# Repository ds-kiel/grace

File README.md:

# IoT-Testbed

A very simple testbed for the IoT!

## GPIO Tracing

Please refer to `raspi/gpio-tracer` for our gpio tracing implementation.

## Installation

### for platform Zoul

It might be necessary to install `pyserial` and `libusb`:

```bash
sudo apt update
sudo apt install python3-pip -y
pip3 install pyserial

sudo apt install libusb-0.1-4
```

### preparation for platform nRF52840

#### COPY JLINK rules file to allow flashing nrf52 for non-root users

```bash
parallel-ssh --timeout 0 --hosts /usr/testbed/scripts/all-hosts --user user --inline "sudo cp /home/user/scripts/nrf52/JLink_Linux_arm/99-jlink.rules /etc/udev/rules.d"
```

#### Flash/Update JLINK Firmware

```bash
parallel-ssh --timeout 0 --hosts /usr/testbed/scripts/all-hosts --user user --inline "sudo -i && cd /home/user/scripts/nrf52 && ./install.sh null.nrf52.hex"
```

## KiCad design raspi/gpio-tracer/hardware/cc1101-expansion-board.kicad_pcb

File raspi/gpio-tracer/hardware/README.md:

# Description
This simple PCB can be used to wire together the development boards for easier
deployment. Alternatively, one can simply wire together everything using jumper wires. We produced
our PCBs at [JLCPCB](https://jlcpcb.com/), look below for our order configuration.
 The schematic files can be opened and exported to gerber files using
[KiCad](https://www.kicad.org/).  You can also look at the schematic for a reference as to how to
wire everything together.

# Hardware
## Receiver
We use a commonly available of-the-shelf cc1101 development board for our setup.  If you want to use
our circuit board for deployment, you need to get a board with the same pin-out configuration.  If
you don't want to use our board and use jumper wires instead, you can get one of the other commonly
available development boards. Just make sure that at least one GPIO (GDx) is exposed.

## Logic Analyzer
Use one of the commonly available ez-usb fx2lp based logic analyzer if you want to use our
PCB. Otherwise, if you jump wire everything you can also use a fx2lp development board.

## Reference Clock
We need one node that emits a reference message every other second. For our setup, we use a
STM32F401CC, but other microcontrollers can easily be adapted to work as reference node as well.

## Miscellaneous
- [2.54mm 10pin Straight Type Box Header](https://www.reichelt.de/wannenstecker-10-polig-gerade-wsl-10g-p22816.html)
- [2.54mm 10pin IDC Socket](https://www.reichelt.de/pfostenbuchse-10-polig-mit-zugentlastung-pfl-10-p14571.html?&trstct=pos_0&nbc=1)
- IDC Ribbon Cable

# PCB Order Configuration

- Base Material: FR-4
- Layers: 2
- Dimension: 65 mm* 56 mm
- PCB Thickness: 1.6
- PCB Color: Green
- Silkscreen: White
- Surface Finish: HASL(with lead)
- Deburring/Edge rounding: No
- Outer Copper Weight: 1
- Gold Fingers: No
- Castellated Holes: no
- Material Type:FR4-Standard Tg 130-140C
- Appearance Quality:IPC Class 2 Standard

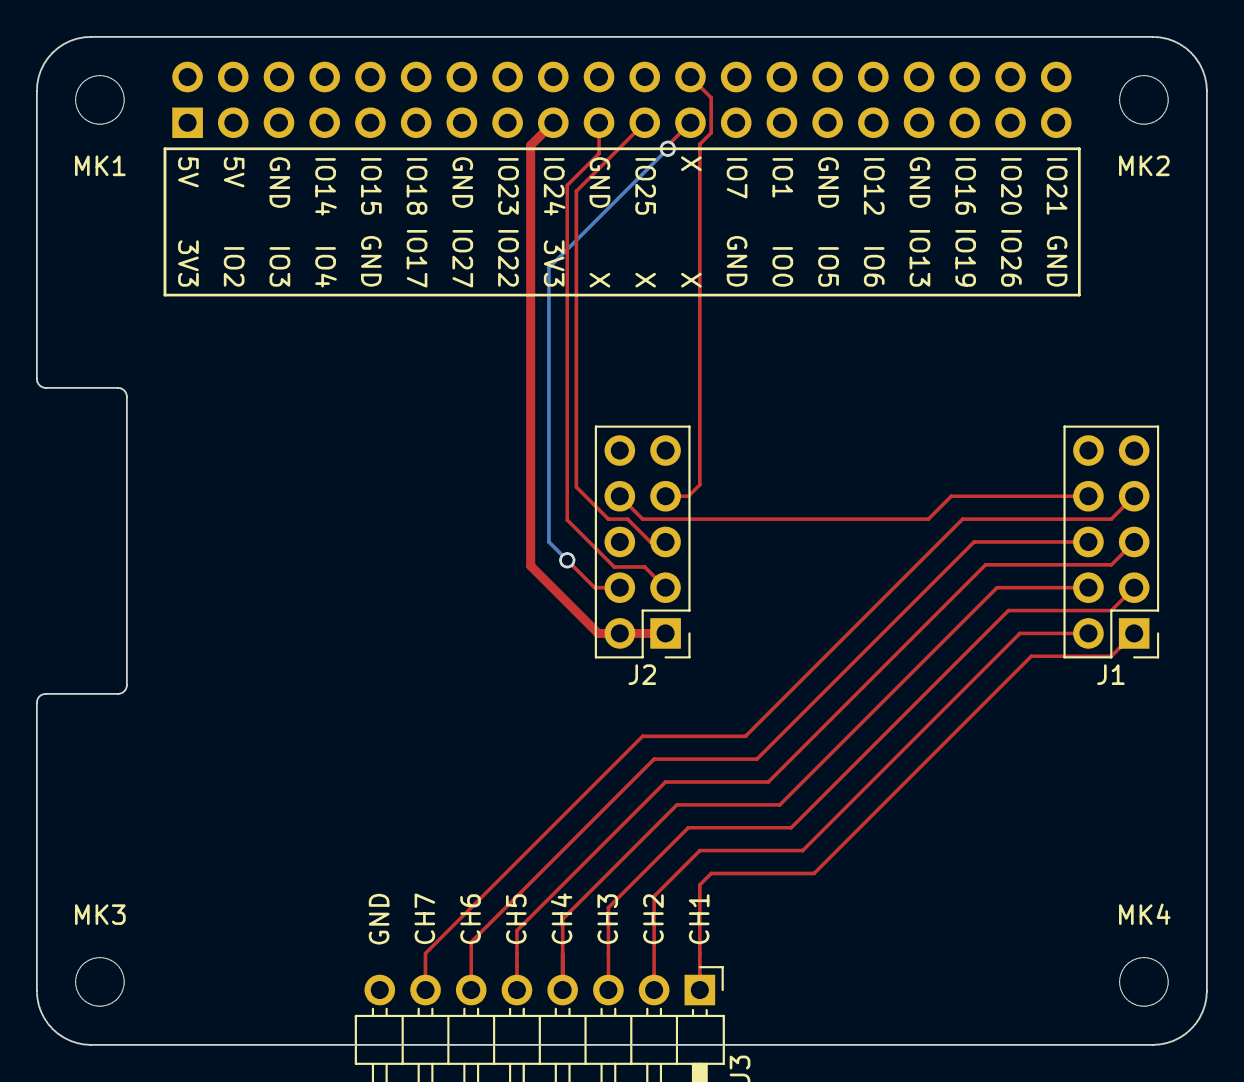
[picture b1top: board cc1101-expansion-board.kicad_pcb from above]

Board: 2 copper layers, 65.0 x 56.0 mm, 8 parts (1 on the bottom side), 15 nets.

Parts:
J1, J2: Conn_02x05_Odd_Even; PinHeader_2x05_P2.54mm_Vertical
J3: Conn_01x08; PinHeader_1x08_P2.54mm_Horizontal
MK1, MK2, MK3, MK4: M2.5; MountingHole_2.7mm_M2.5
P1: Conn_02x20_Odd_Even; PinSocket_2x20_P2.54mm_Vertical

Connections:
+3V3: J2.1, J2.2, P1.1, P1.17
+5V: P1.2, P1.4
/CH1: J1.1, J3.1
/CH2: J1.2, J3.2
/CH3: J1.3, J3.3
/CH4: J1.4, J3.4
/CH5: J1.5, J3.5
/CH6: J1.6, J3.6
/CH7: J1.7, J3.7
/CH8: J1.8, J2.8
/CSN: J2.7, P1.24
/SCK: J2.4, P1.23
/SI: J2.3, P1.19
/SO: J2.5, P1.21
GND: J1.10, J2.9, J2.10, J3.8, P1.6, P1.9, P1.14, P1.20, P1.25, P1.30, P1.34, P1.39

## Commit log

2020-05-28 Initial commit logic-analyzer c backend
2020-05-29 Add timestamps to traces
2020-06-02 Use timespec structure
2020-06-03 Added some more resources
2020-06-09 added pigpio
2020-06-09 Added Dockerfile for testbed.py development
2020-06-10 basic setup for daemon/client split
2020-06-10 added --start --stop arguments to gpiotc
2020-06-10 Fixed argument reading
2020-06-11 added gpio-tracer to zoul and sky start script
2020-06-30 wip support saleae and sigrok through daemon
2020-06-30 wip: added GPIOT_DEVICE_NONE + some bug fixes
2020-07-02 use more glib and use dbus instead of unix domain sockets for ipc
2020-07-02 Allow killing of sigrok instance after session stop
2020-07-02 Added files to start gpiot as a systemd service on the d-bus system bus
2020-07-02 fixed default logpath and minor bug in return of result for stop method
2020-07-06 seperate nanosecond and second output
2020-07-07 Fixed printf output bug on raspberry pi
2020-07-07 output timestamps as nanosecond
2020-07-09 output gpio traces in the same format as flocklab
2020-07-09 WIP Actuate transmitter from gpiotd
2020-07-09 fixed output
2020-07-10 don't create session bus
2020-07-14 fixed some instance stop bugs
2020-07-14 Use channel 2 of the logic analyzer for pps signal capture
2020-07-15 reinit variables on instance kill
2020-07-19 found working transmitter parameters
2020-07-19 fixed script start command
2020-07-19 WIP: add sync nodes and collector nodes
2020-07-20 WIP: added transmitter shared library
    Added so an accurate timed pulse can be send from python
2020-07-20 WIP: added systemd services
2020-07-20 WIP: updated readme with dependencies
2020-07-20 WIP: expect atleast 5 sync packages
2020-07-20 WIP: found some first good parameters for sync pulse
2020-07-20 Removed garbage files
2020-07-21 WIP: collectors can be configured to wait for sync pulse
2020-07-21 WIP: sync node starts nodes and collects timestamps
2020-07-21 WIP: removed pigpio la
2020-07-21 WIP: removed reference to la-pigpio.c from lib/CMakeLists.txt
2020-07-22 WIP: added files for deployment on raspbian stretch
2020-07-22 WIP: fixed deployment scheme
2020-07-23 WIP: fixed various bugs
2020-07-23 WIP: get factors from sync node
2020-07-24 added sync node wrapper for debian stretch
2020-07-31 WIP: collect timestamps
2020-08-01 Added exaple for possible testbed interface integration
2020-08-03 shuffle around column format
2020-11-26 preparing move to python3
2020-11-26 changing raise to python3 format
2020-11-26 print formatting python3
2020-11-26 wxcept formatting python3
2020-11-26 python3 formatting
2020-11-28 Added Sync command
2020-12-08 Deleted files that are not necessary anymore
2020-12-09 removed old code
2020-12-09 preparation for new code structure
2020-12-19 Pass GAsyncQueue to postprocess thread
2021-01-02 added radio_master & radio_slave; initialize threads
2021-01-05 Working radio_master implemention. Fixing timestamps with correction factor
2021-01-18 fixing list function in testbed.py (Python 3 specific)
2021-01-22 Fix timestamps with reference timestamps from receiver
2021-01-22 Increased reference timestamp frequency; fixed thread initialization
2021-01-27 Increased radio_slave wait time while waiting for package reception
2021-02-16 Assert GP0 on successfull package reception
2021-02-17 Fixed transmitter deadlock and removed some console logging
2021-03-08 Check wether transceiver went into IDLE because of discarded packet
2021-03-20 WIP: closed loop control w/ floating points
2021-03-21 WIP: open-loop frequency, closed-loop offset
2021-04-06 WIP: threadless output module
2021-04-07 WIP: make output efficient
2021-05-22 partially replaced g_printf with g_debug; fixed bug in radio;
2021-05-25 WIP: Added more logging, fixed output, added radio_deinit
2021-06-15 WIP: closed & open feedback loop with adjustable internal precision
2021-06-22 truncate last output chunk after finished tracing
2021-06-30 Renamed preprocess -> tracing; added more installation instruction
2021-10-07 Added more installation details; don't run gpiotd as root
2021-10-12 added enumeration of candidate fx2 devices
2021-10-13 Upload/Download firmware from fx2
2021-10-23 Continously commit bulk transfers from FX2 to host
2021-10-23 use glib types where possible
2021-10-23 reduced maximum amount of bytes per control transfer
2021-10-23 keep Bus busy by submitting multiple transfers
2021-11-02 Added callback handler for incoming packets. use fx2 in tracing
2021-11-02 Added preliminary working fx2 firmware
2021-11-07 added test_tracing test program; WIP: firmware soft spi
2021-11-11 make gpiotd work with new code structure
2021-11-13 Reset device on failed usb transfer
2021-11-25 Added firmware for stm32; build firmware with platformio
2021-12-09 WIP: stm32 <-> fx2 communication
2021-12-22 radio: added structure containing the transceiver options
2021-12-22 WIP: enabled EP1IN and EP1OUT
2021-12-22 WIP: added EP1IN and EP1OUT descriptors to dscr.a51
2021-12-22 WIP: Added high sense configuration
2022-01-13 Adding serial forwarding for zoul
2022-01-14 WIP: EP1IN and EP1OUT for communication with mcu
2022-01-21 WIP: automatically reduce sampling rate when data stream drops unexpectedly
2022-02-25 fix serial forwarding when not using '--start'
2022-04-01 Add serial forwarder functionality for selected nodes
2022-04-01 use python3 for installing zoul firmware
2022-04-04 fix serial host forwarding file creation
2022-04-25 auto scale frequency on connection drop
2022-04-25 reinit radio before restarting tracing
2022-04-25 fixed gpiotd and test_tracing segfault
2022-05-19 Added utility applications
2022-05-24 Added hardware files for simple connector board
2022-05-24 WIP: Build fx2 firmware with platformio
2022-05-24 Added hardware README; Pull fx2lib from github
2022-05-24 added targets for building bix and iix files
2022-05-24 pass xram location from board config to linker
2022-05-26 Added more explanation to hardware README
2022-05-26 Fixed cc1101 image path
2022-05-26 Updated gpio-tracer README
2022-05-26 Added instruction for building firmware
2022-05-26 Use shell code blocks for README
2022-05-26 README: make it pretty
2022-05-26 Added README for stm32 firmware
2022-05-26 Pass firmware location to gpiotd through argument
2022-05-26 Added logic analyzer and testbed node image
2022-05-26 reduced image size
2022-05-26 further reduced images sizes for other images
2022-05-26 Fix image placement
2022-05-26 WIP: add reference clock instructions
2022-05-26 Refer to gpio tracing from README
2022-05-26 Deleted unrelevant comments
2022-05-27 Update install instructions
2022-07-11 Add setup steps for nRF52840
2022-08-02 Fix path error
2022-09-21 Updated testbed.py script
2022-09-23 Cosmetics changes; Read test_tracing arguments through glib
